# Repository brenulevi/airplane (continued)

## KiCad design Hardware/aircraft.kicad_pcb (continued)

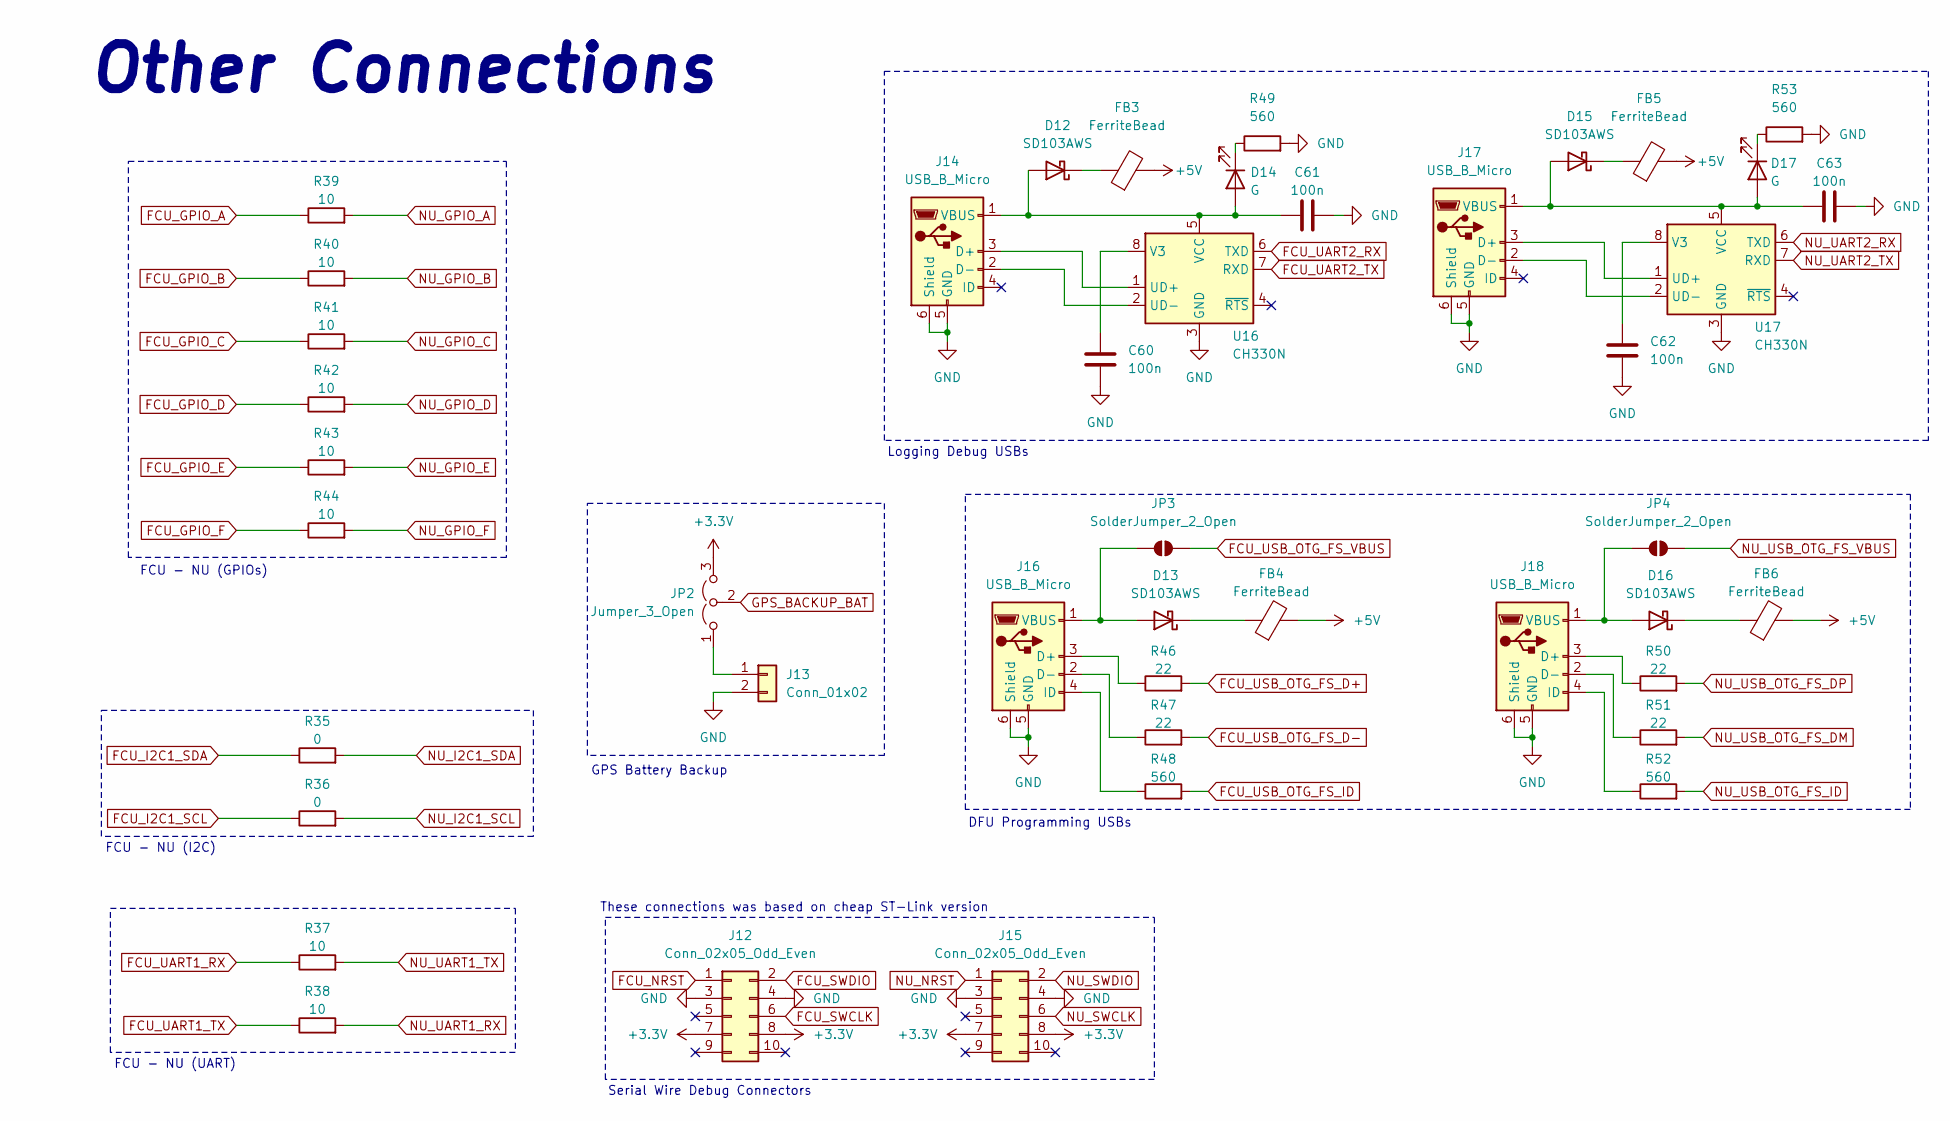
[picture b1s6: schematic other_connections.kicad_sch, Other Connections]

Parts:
C60, C62: 100n; C_0402_1005Metric; MPN C0603C104K8RACTU
C61, C63: 100n; C_0603_1608Metric; MPN C0603C104K8RACTU
D12, D13, D15, D16: SD103AWS; D_SOD-323_HandSoldering; MPN SD103AWS
D14, D17: G; LED_0402_1005Metric; MPN LTST-S270KGKT
FB3, FB4, FB5, FB6: FerriteBead; L_0603_1608Metric; MPN HZ0805E601R-10
J12, J15: Conn_02x05_Odd_Even; JST_PHD_B10B-PHDSS_2x05_P2.00mm_Vertical; MPN B10B-PHDSS
J13: Conn_01x02; JST_PH_S2B-PH-K_1x02_P2.00mm_Horizontal; MPN S2B-PH-K-S
J14, J16, J17, J18: USB_B_Micro; USB_Micro-B_Molex_47346-0001; MPN 0473461001
JP2: Jumper_3_Open; SolderJumper-3_P1.3mm_Open_RoundedPad1.0x1.5mm_NumberLabels
JP3, JP4: SolderJumper_2_Open; SolderJumper-2_P1.3mm_Open_RoundedPad1.0x1.5mm
R35, R36: 0; R_0402_1005Metric; MPN RC0603JR-070RL
R37, R38, R39, R40, R41, R42, R43, R44: 10; R_0402_1005Metric; MPN RMCF0603FT10R0
R46, R47, R50, R51: 22; R_0402_1005Metric; MPN RC0603FR-0722RL
R48, R49, R52, R53: 560; R_0402_1005Metric; MPN RMCF0603FT560R
U16, U17: CH330N; SOIC-8_3.9x4.9mm_P1.27mm; MPN CH330N

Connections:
+3.3V: J12.7, J12.8, J15.7, J15.8, JP2.3 (B); also elsewhere on the board
+5V: FB3.2, FB4.2, FB5.2, FB6.2; also elsewhere on the board
FCU_GPIO_A: R39.1; also elsewhere on the board
FCU_GPIO_B: R40.1; also elsewhere on the board
FCU_GPIO_C: R41.1; also elsewhere on the board
FCU_GPIO_D: R42.1; also elsewhere on the board
FCU_GPIO_E: R43.1; also elsewhere on the board
FCU_GPIO_F: R44.1; also elsewhere on the board
FCU_I2C1_SCL: R36.1; also elsewhere on the board
FCU_I2C1_SDA: R35.1; also elsewhere on the board
FCU_NRST: J12.1; also elsewhere on the board
FCU_SWCLK: J12.6; also elsewhere on the board
FCU_SWDIO: J12.2; also elsewhere on the board
FCU_UART1_RX: R37.1; also elsewhere on the board
FCU_UART1_TX: R38.1; also elsewhere on the board
FCU_UART2_RX: U16.6 (TXD); also elsewhere on the board
FCU_UART2_TX: U16.7 (RXD); also elsewhere on the board
FCU_USB_OTG_FS_D+: R46.2; also elsewhere on the board
FCU_USB_OTG_FS_D-: R47.2; also elsewhere on the board
FCU_USB_OTG_FS_ID: R48.2; also elsewhere on the board
FCU_USB_OTG_FS_VBUS: JP3.2 (B); also elsewhere on the board
GND: C60.2, C61.2, C62.2, C63.2, J12.3, J12.4, J13.2, J14.5 (GND), J14.6 (Shield), J15.3, J15.4, J16.5 (GND), J16.6 (Shield), J17.5 (GND), J17.6 (Shield), J18.5 (GND), J18.6 (Shield), R49.2, R53.2, U16.3 (GND), U17.3 (GND); also elsewhere on the board
GPS_BACKUP_BAT: JP2.2 (C); also elsewhere on the board
NU_GPIO_A: R39.2; also elsewhere on the board
NU_GPIO_B: R40.2; also elsewhere on the board
NU_GPIO_C: R41.2; also elsewhere on the board
NU_GPIO_D: R42.2; also elsewhere on the board
NU_GPIO_E: R43.2; also elsewhere on the board
NU_GPIO_F: R44.2; also elsewhere on the board
NU_I2C1_SCL: R36.2; also elsewhere on the board
NU_I2C1_SDA: R35.2; also elsewhere on the board
NU_NRST: J15.1; also elsewhere on the board
NU_SWCLK: J15.6; also elsewhere on the board
NU_SWDIO: J15.2; also elsewhere on the board
NU_UART1_RX: R38.2; also elsewhere on the board
NU_UART1_TX: R37.2; also elsewhere on the board
NU_UART2_RX: U17.6 (TXD); also elsewhere on the board
NU_UART2_TX: U17.7 (RXD); also elsewhere on the board
NU_USB_OTG_FS_DM: R51.2; also elsewhere on the board
NU_USB_OTG_FS_DP: R50.2; also elsewhere on the board
NU_USB_OTG_FS_ID: R52.2; also elsewhere on the board
NU_USB_OTG_FS_VBUS: JP4.2 (B); also elsewhere on the board
unnamed: C61.1, D12.2 (A), D14.2 (A), J14.1 (VBUS), U16.5 (VCC)
unnamed: D12.1 (K), FB3.1
unnamed: D13.2 (A), J16.1 (VBUS), JP3.1 (A)
unnamed: D13.1 (K), FB4.1
unnamed: D14.1 (K), R49.1
unnamed: C63.1, D15.2 (A), D17.2 (A), J17.1 (VBUS), U17.5 (VCC)
unnamed: D15.1 (K), FB5.1
unnamed: D16.2 (A), J18.1 (VBUS), JP4.1 (A)
unnamed: D16.1 (K), FB6.1
unnamed: D17.1 (K), R53.1
unnamed: J13.1, JP2.1 (A)
unnamed: J14.3 (D+), U16.1 (UD+)
unnamed: J14.2 (D-), U16.2 (UD-)
unnamed: J16.3 (D+), R46.1
unnamed: J16.2 (D-), R47.1
unnamed: J16.4 (ID), R48.1
unnamed: J17.3 (D+), U17.1 (UD+)
unnamed: J17.2 (D-), U17.2 (UD-)
unnamed: J18.3 (D+), R50.1
unnamed: J18.2 (D-), R51.1
unnamed: J18.4 (ID), R52.1
unnamed: C60.1, U16.8 (V3)
unnamed: C62.1, U17.8 (V3)

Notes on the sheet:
FCU - NU (GPIOs)
Serial Wire Debug Connectors
Other Connections
DFU Programming USBs
GPS Battery Backup
FCU - NU (I2C)
These connections was based on cheap ST-Link version
Logging Debug USBs
FCU - NU (UART)

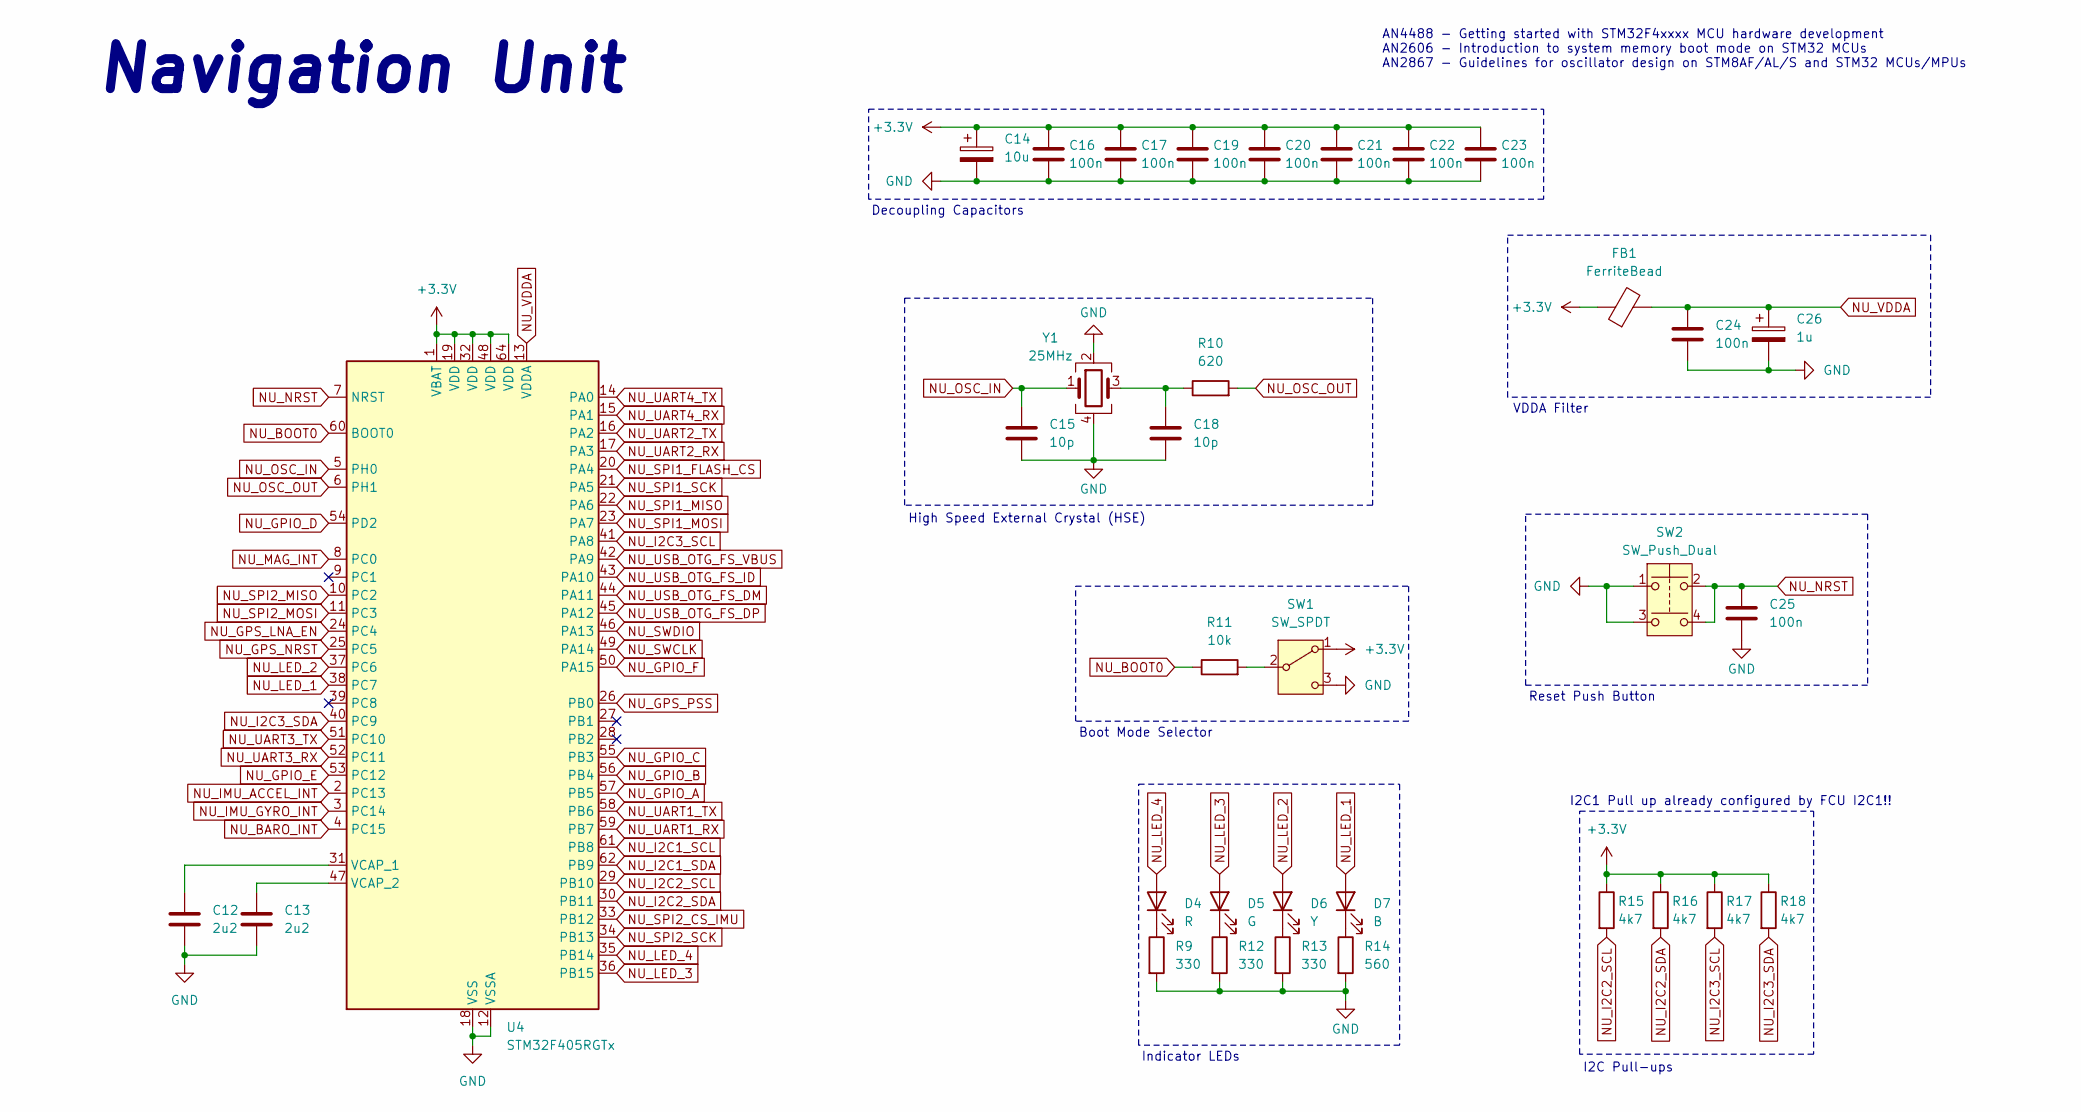
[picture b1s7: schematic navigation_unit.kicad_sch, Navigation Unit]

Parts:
C12, C13: 2u2; C_0603_1608Metric; MPN CL10B225KP8NNNC
C14: 10u; C_1206_3216Metric_Pad1.33x1.80mm_HandSolder; MPN TAJA106K010TNJ
C15, C18: 10p; C_0402_1005Metric; MPN 885012005007
C16, C17, C19, C20, C21, C22, C23, C24: 100n; C_0402_1005Metric; MPN CL05B104KP5NNNC
C25: 100n; C_0603_1608Metric; MPN C0603C104K8RACTU
C26: 1u; CP_EIA-1608-08_AVX-J; MPN T491A105K010AT
D4: R; LED_0805_2012Metric_Pad1.15x1.40mm_HandSolder; MPN LTST-C171KRKT
D5: G; LED_0805_2012Metric_Pad1.15x1.40mm_HandSolder; MPN LTST-C170GKT
D6: Y; LED_0805_2012Metric_Pad1.15x1.40mm_HandSolder; MPN LTST-C171YKT
D7: B; LED_0805_2012Metric_Pad1.15x1.40mm_HandSolder; MPN LTST-C171TBKT
FB1: FerriteBead; L_0805_2012Metric_Pad1.05x1.20mm_HandSolder; MPN HZ0805E601R-10
R9, R12, R13: 330; R_0603_1608Metric_Pad0.98x0.95mm_HandSolder; MPN RC0603JR-07330RL
R10: 620; R_0603_1608Metric_Pad0.98x0.95mm_HandSolder; MPN RC0603FR-07620RL
R11: 10k; R_0603_1608Metric_Pad0.98x0.95mm_HandSolder; MPN RC0603FR-0710KL
R14: 560; R_0603_1608Metric_Pad0.98x0.95mm_HandSolder; MPN RMCF0603FT560R
R15, R16, R17, R18: 4k7; R_0603_1608Metric_Pad0.98x0.95mm_HandSolder; MPN ERJ-3EKF4701V
SW1: SW_SPDT; SW_SPDT_PCM12; MPN PCM12SMTR
SW2: SW_Push_Dual; SW4_PTS815 SJM 250 SMTR LFS_CNK; MPN PTS815SJM250SMTRLFS
U4: STM32F405RGTx; LQFP-64_10x10mm_P0.5mm; MPN STM32F405RGT6
Y1: 25MHz; Crystal_SMD_Abracon_ABM8G-4Pin_3.2x2.5mm; MPN ABM8G-25.000MHZ-B4Y-T3

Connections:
+3.3V: C14.1, C16.1, C17.1, C19.1, C20.1, C21.1, C22.1, C23.1, FB1.1, R15.1, R16.1, R17.1, R18.1, SW1.1 (A), U4.1 (VBAT), U4.19 (VDD), U4.32 (VDD), U4.48 (VDD), U4.64 (VDD); also elsewhere on the board
GND: C12.2, C13.2, C14.2, C15.2, C16.2, C17.2, C18.2, C19.2, C20.2, C21.2, C22.2, C23.2, C24.2, C25.2, C26.2, R9.2, R12.2, R13.2, R14.2, SW1.3 (C), SW2.1, SW2.3, U4.12 (VSSA), U4.18 (VSS), U4.63 (VSS), Y1.2, Y1.4; also elsewhere on the board
NU_BARO_INT: U4.4 (PC15); also elsewhere on the board
NU_BOOT0: R11.1, U4.60 (BOOT0)
NU_GPIO_A: U4.57 (PB5); also elsewhere on the board
NU_GPIO_B: U4.56 (PB4); also elsewhere on the board
NU_GPIO_C: U4.55 (PB3); also elsewhere on the board
NU_GPIO_D: U4.54 (PD2); also elsewhere on the board
NU_GPIO_E: U4.53 (PC12); also elsewhere on the board
NU_GPIO_F: U4.50 (PA15); also elsewhere on the board
NU_GPS_LNA_EN: U4.24 (PC4); also elsewhere on the board
NU_GPS_NRST: U4.25 (PC5); also elsewhere on the board
NU_GPS_PSS: U4.26 (PB0); also elsewhere on the board
NU_I2C1_SCL: U4.61 (PB8); also elsewhere on the board
NU_I2C1_SDA: U4.62 (PB9); also elsewhere on the board
NU_I2C2_SCL: R15.2, U4.29 (PB10); also elsewhere on the board
NU_I2C2_SDA: R16.2, U4.30 (PB11); also elsewhere on the board
NU_I2C3_SCL: R17.2, U4.41 (PA8); also elsewhere on the board
NU_I2C3_SDA: R18.2, U4.40 (PC9); also elsewhere on the board
NU_IMU_ACCEL_INT: U4.2 (PC13); also elsewhere on the board
NU_IMU_GYRO_INT: U4.3 (PC14); also elsewhere on the board
NU_LED_1: D7.2 (A), U4.38 (PC7)
NU_LED_2: D6.2 (A), U4.37 (PC6)
NU_LED_3: D5.2 (A), U4.36 (PB15)
NU_LED_4: D4.2 (A), U4.35 (PB14)
NU_MAG_INT: U4.8 (PC0); also elsewhere on the board
NU_NRST: C25.1, SW2.2, SW2.4, U4.7 (NRST); also elsewhere on the board
NU_OSC_IN: C15.1, U4.5 (PH0), Y1.1
NU_OSC_OUT: R10.2, U4.6 (PH1)
NU_SPI1_FLASH_CS: U4.20 (PA4); also elsewhere on the board
NU_SPI1_MISO: U4.22 (PA6); also elsewhere on the board
NU_SPI1_MOSI: U4.23 (PA7); also elsewhere on the board
NU_SPI1_SCK: U4.21 (PA5); also elsewhere on the board
NU_SPI2_CS_IMU: U4.33 (PB12)
NU_SPI2_MISO: U4.10 (PC2)
NU_SPI2_MOSI: U4.11 (PC3)
NU_SPI2_SCK: U4.34 (PB13)
NU_SWCLK: U4.49 (PA14); also elsewhere on the board
NU_SWDIO: U4.46 (PA13); also elsewhere on the board
NU_UART1_RX: U4.59 (PB7); also elsewhere on the board
NU_UART1_TX: U4.58 (PB6); also elsewhere on the board
NU_UART2_RX: U4.17 (PA3); also elsewhere on the board
NU_UART2_TX: U4.16 (PA2); also elsewhere on the board
NU_UART3_RX: U4.52 (PC11); also elsewhere on the board
NU_UART3_TX: U4.51 (PC10); also elsewhere on the board
NU_UART4_RX: U4.15 (PA1); also elsewhere on the board
NU_UART4_TX: U4.14 (PA0); also elsewhere on the board
NU_USB_OTG_FS_DM: U4.44 (PA11); also elsewhere on the board
NU_USB_OTG_FS_DP: U4.45 (PA12); also elsewhere on the board
NU_USB_OTG_FS_ID: U4.43 (PA10); also elsewhere on the board
NU_USB_OTG_FS_VBUS: U4.42 (PA9); also elsewhere on the board
NU_VDDA: C24.1, C26.1, FB1.2, U4.13 (VDDA)
unnamed: C18.1, R10.1, Y1.3
unnamed: D4.1 (K), R9.1
unnamed: D5.1 (K), R12.1
unnamed: D6.1 (K), R13.1
unnamed: D7.1 (K), R14.1
unnamed: R11.2, SW1.2 (B)
unnamed: C12.1, U4.31 (VCAP_1)
unnamed: C13.1, U4.47 (VCAP_2)

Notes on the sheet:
Decoupling Capacitors
I2C Pull-ups
Indicator LEDs
I2C1 Pull up already configured by FCU I2C1!!
Reset Push Button
Boot Mode Selector
VDDA Filter
AN4488 - Getting started with STM32F4xxxx MCU hardware development AN2606 - Introduction to system memory boot mode on STM32 MCUs AN2867 - Guidelines for oscillator design on STM8AF/AL/S and STM32 MCUs/MPUs
Navigation Unit
High Speed External Crystal (HSE)

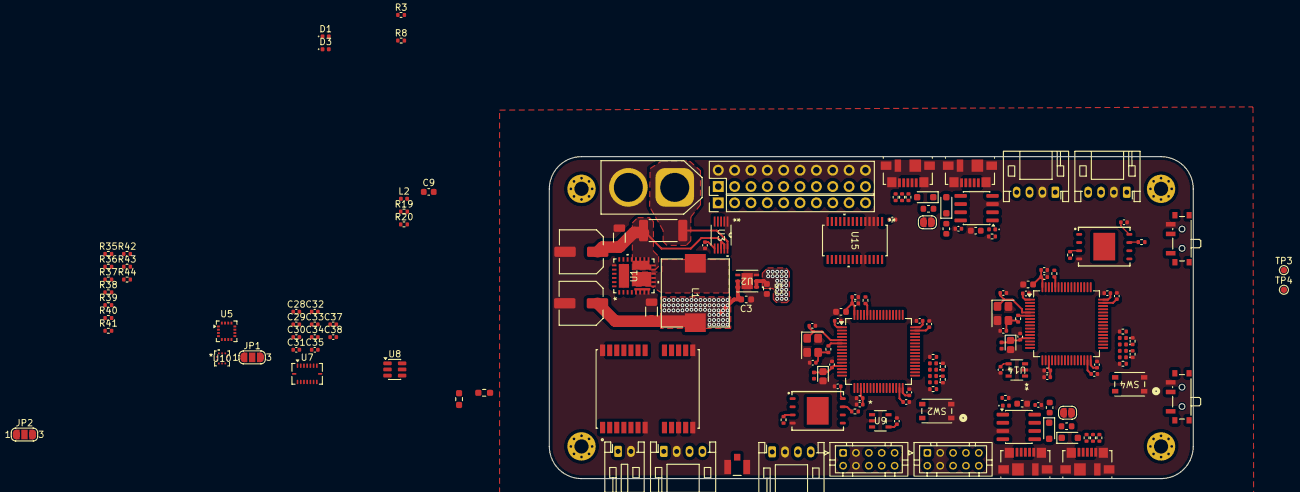
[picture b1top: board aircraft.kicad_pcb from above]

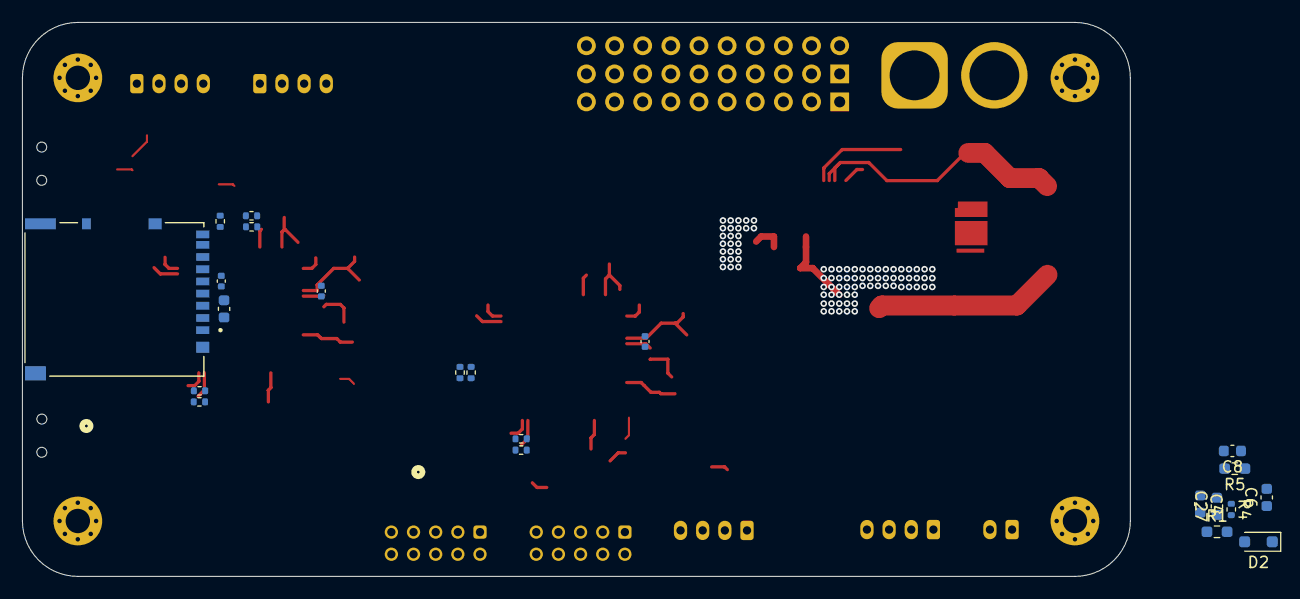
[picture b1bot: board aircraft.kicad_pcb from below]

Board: 4 copper layers, 100.0 x 50.0 mm, 186 parts (22 on the bottom side), 161 nets.

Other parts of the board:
R45: 10m; R_2512_6332Metric_Pad1.40x3.35mm_HandSolder

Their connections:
PS_PVIN: R45.1; also elsewhere on the board
VIN+: R45.2; also elsewhere on the board

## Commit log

2026-01-14 power supply and navigation unit
2026-01-17 fixed some errors in global labels
2026-01-17 updated schematic pdf
2026-01-23 hardware version 0.1.2, minor improvements and footprint selection (missing some gnss and bulk regulator components
2026-01-26 board placement, no trails, just pain
2026-01-27 hardware: better layout, no power supply and sensors
2026-01-28 fill zones done, layout reformulation because of 5v, power supply power traces done
